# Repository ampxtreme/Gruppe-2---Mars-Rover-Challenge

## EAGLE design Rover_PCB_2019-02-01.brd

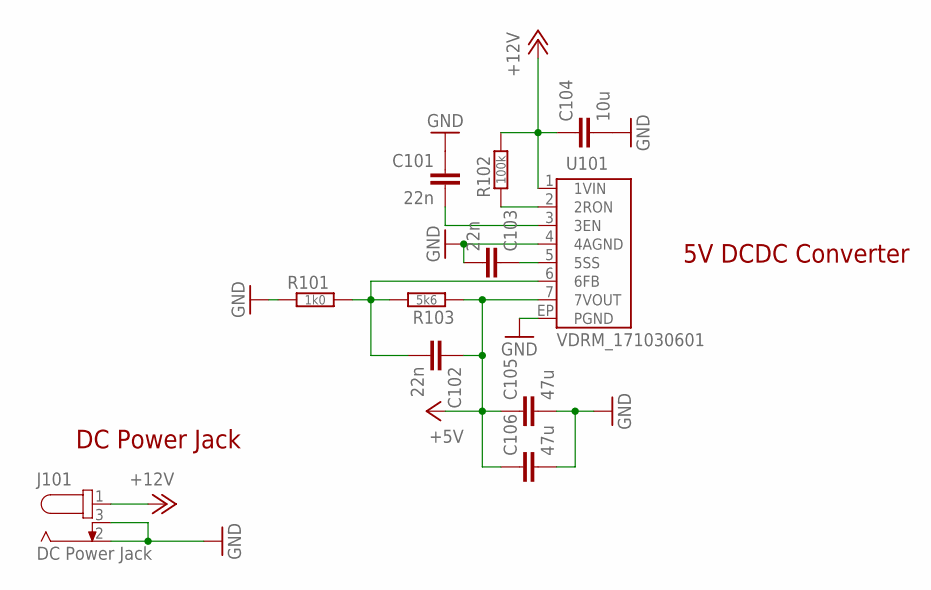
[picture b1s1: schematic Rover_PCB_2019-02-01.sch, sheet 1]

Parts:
C101, C102, C103: 22n; CAPC2012X95N
C104: 10u; CAP-US1210-EU3225
C105, C106: 47u; CAP-US1210-EU3225
J101: DC Power Jack; 69410X105102
R101: 1k0; RESC2012X50N
R102: 100k; RESC2012X50N
R103: 5k6; RESC2012X50N
U101: VDRM_171030601; VDRM_7PIN-PFM

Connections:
+5V: C102.1, C105.1, C106.1, R103.1, U101.7 (7VOUT); also elsewhere on the board
+12V: C104.1, J101.1, R102.2, U101.1 (1VIN); also elsewhere on the board
GND: C101.1, C103.2, C104.2, C105.2, C106.2, J101.2, J101.3, R101.1, U101.4 (4AGND), U101.EP (PGND); also elsewhere on the board
unnamed: R102.1, U101.2 (2RON)
unnamed: C103.1, U101.5 (5SS)
unnamed: C102.2, R101.2, R103.2, U101.6 (6FB)
unnamed: C101.2, U101.3 (3EN)

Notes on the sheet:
5V DCDC Converter
DC Power Jack

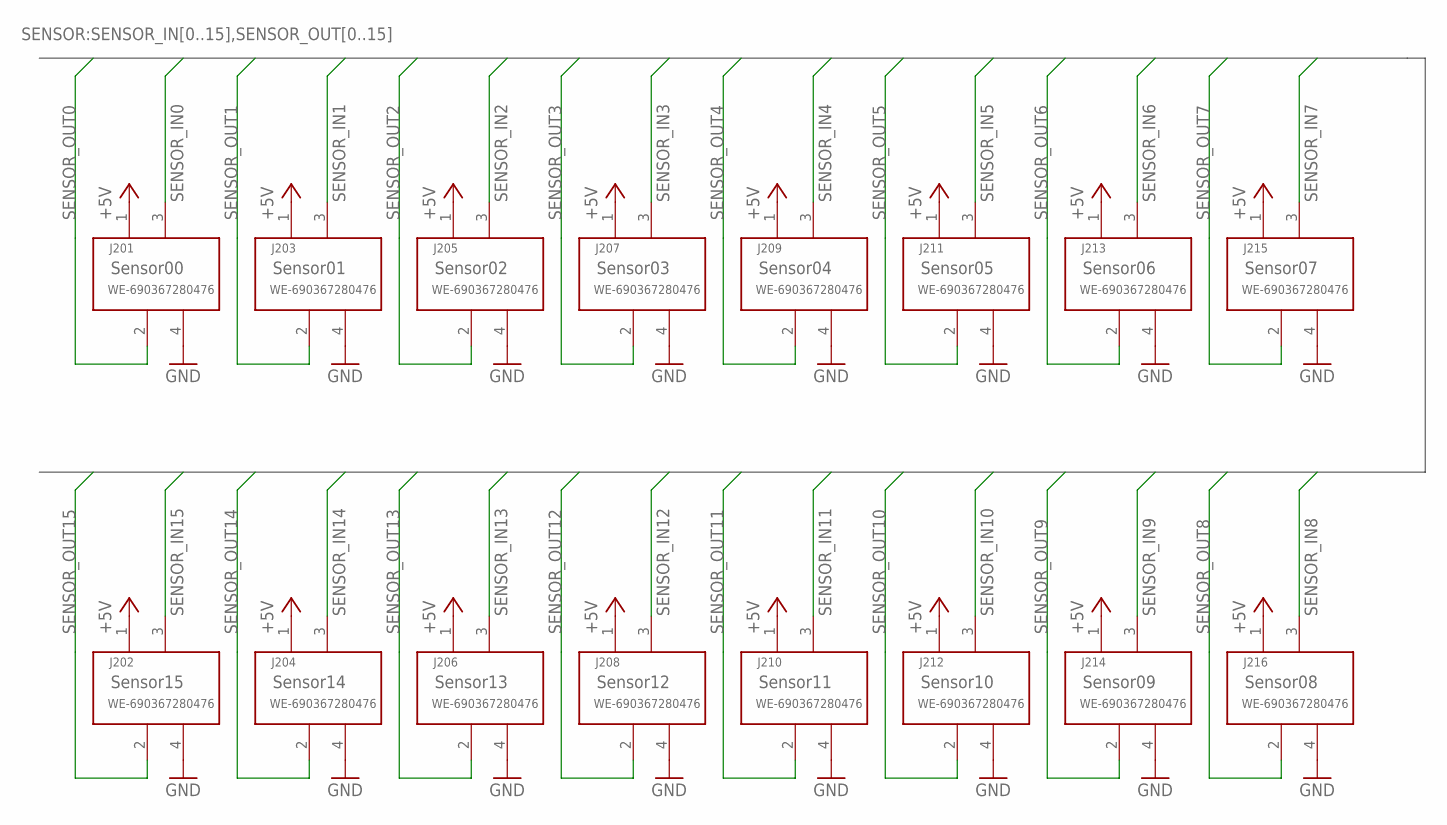
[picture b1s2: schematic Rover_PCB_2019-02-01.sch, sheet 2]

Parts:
J201, J202, J203, J204, J205, J206, J207, J208, J209, J210, J211, J212, J213, J214, J215, J216: WE-690367280476; 690367280476

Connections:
+5V: J201.1 (4), J202.1 (4), J203.1 (4), J204.1 (4), J205.1 (4), J206.1 (4), J207.1 (4), J208.1 (4), J209.1 (4), J210.1 (4), J211.1 (4), J212.1 (4), J213.1 (4), J214.1 (4), J215.1 (4), J216.1 (4); also elsewhere on the board
GND: J201.4 (1), J202.4 (1), J203.4 (1), J204.4 (1), J205.4 (1), J206.4 (1), J207.4 (1), J208.4 (1), J209.4 (1), J210.4 (1), J211.4 (1), J212.4 (1), J213.4 (1), J214.4 (1), J215.4 (1), J216.4 (1); also elsewhere on the board
SENSOR_IN0: J201.3 (2); also elsewhere on the board
SENSOR_IN1: J203.3 (2); also elsewhere on the board
SENSOR_IN2: J205.3 (2); also elsewhere on the board
SENSOR_IN3: J207.3 (2); also elsewhere on the board
SENSOR_IN4: J209.3 (2); also elsewhere on the board
SENSOR_IN5: J211.3 (2); also elsewhere on the board
SENSOR_IN6: J213.3 (2); also elsewhere on the board
SENSOR_IN7: J215.3 (2); also elsewhere on the board
SENSOR_IN8: J216.3 (2); also elsewhere on the board
SENSOR_IN9: J214.3 (2); also elsewhere on the board
SENSOR_IN10: J212.3 (2); also elsewhere on the board
SENSOR_IN11: J210.3 (2); also elsewhere on the board
SENSOR_IN12: J208.3 (2); also elsewhere on the board
SENSOR_IN13: J206.3 (2); also elsewhere on the board
SENSOR_IN14: J204.3 (2); also elsewhere on the board
SENSOR_IN15: J202.3 (2); also elsewhere on the board
SENSOR_OUT0: J201.2 (3); also elsewhere on the board
SENSOR_OUT1: J203.2 (3); also elsewhere on the board
SENSOR_OUT2: J205.2 (3); also elsewhere on the board
SENSOR_OUT3: J207.2 (3); also elsewhere on the board
SENSOR_OUT4: J209.2 (3); also elsewhere on the board
SENSOR_OUT5: J211.2 (3); also elsewhere on the board
SENSOR_OUT6: J213.2 (3); also elsewhere on the board
SENSOR_OUT7: J215.2 (3); also elsewhere on the board
SENSOR_OUT8: J216.2 (3); also elsewhere on the board
SENSOR_OUT9: J214.2 (3); also elsewhere on the board
SENSOR_OUT10: J212.2 (3); also elsewhere on the board
SENSOR_OUT11: J210.2 (3); also elsewhere on the board
SENSOR_OUT12: J208.2 (3); also elsewhere on the board
SENSOR_OUT13: J206.2 (3); also elsewhere on the board
SENSOR_OUT14: J204.2 (3); also elsewhere on the board
SENSOR_OUT15: J202.2 (3); also elsewhere on the board

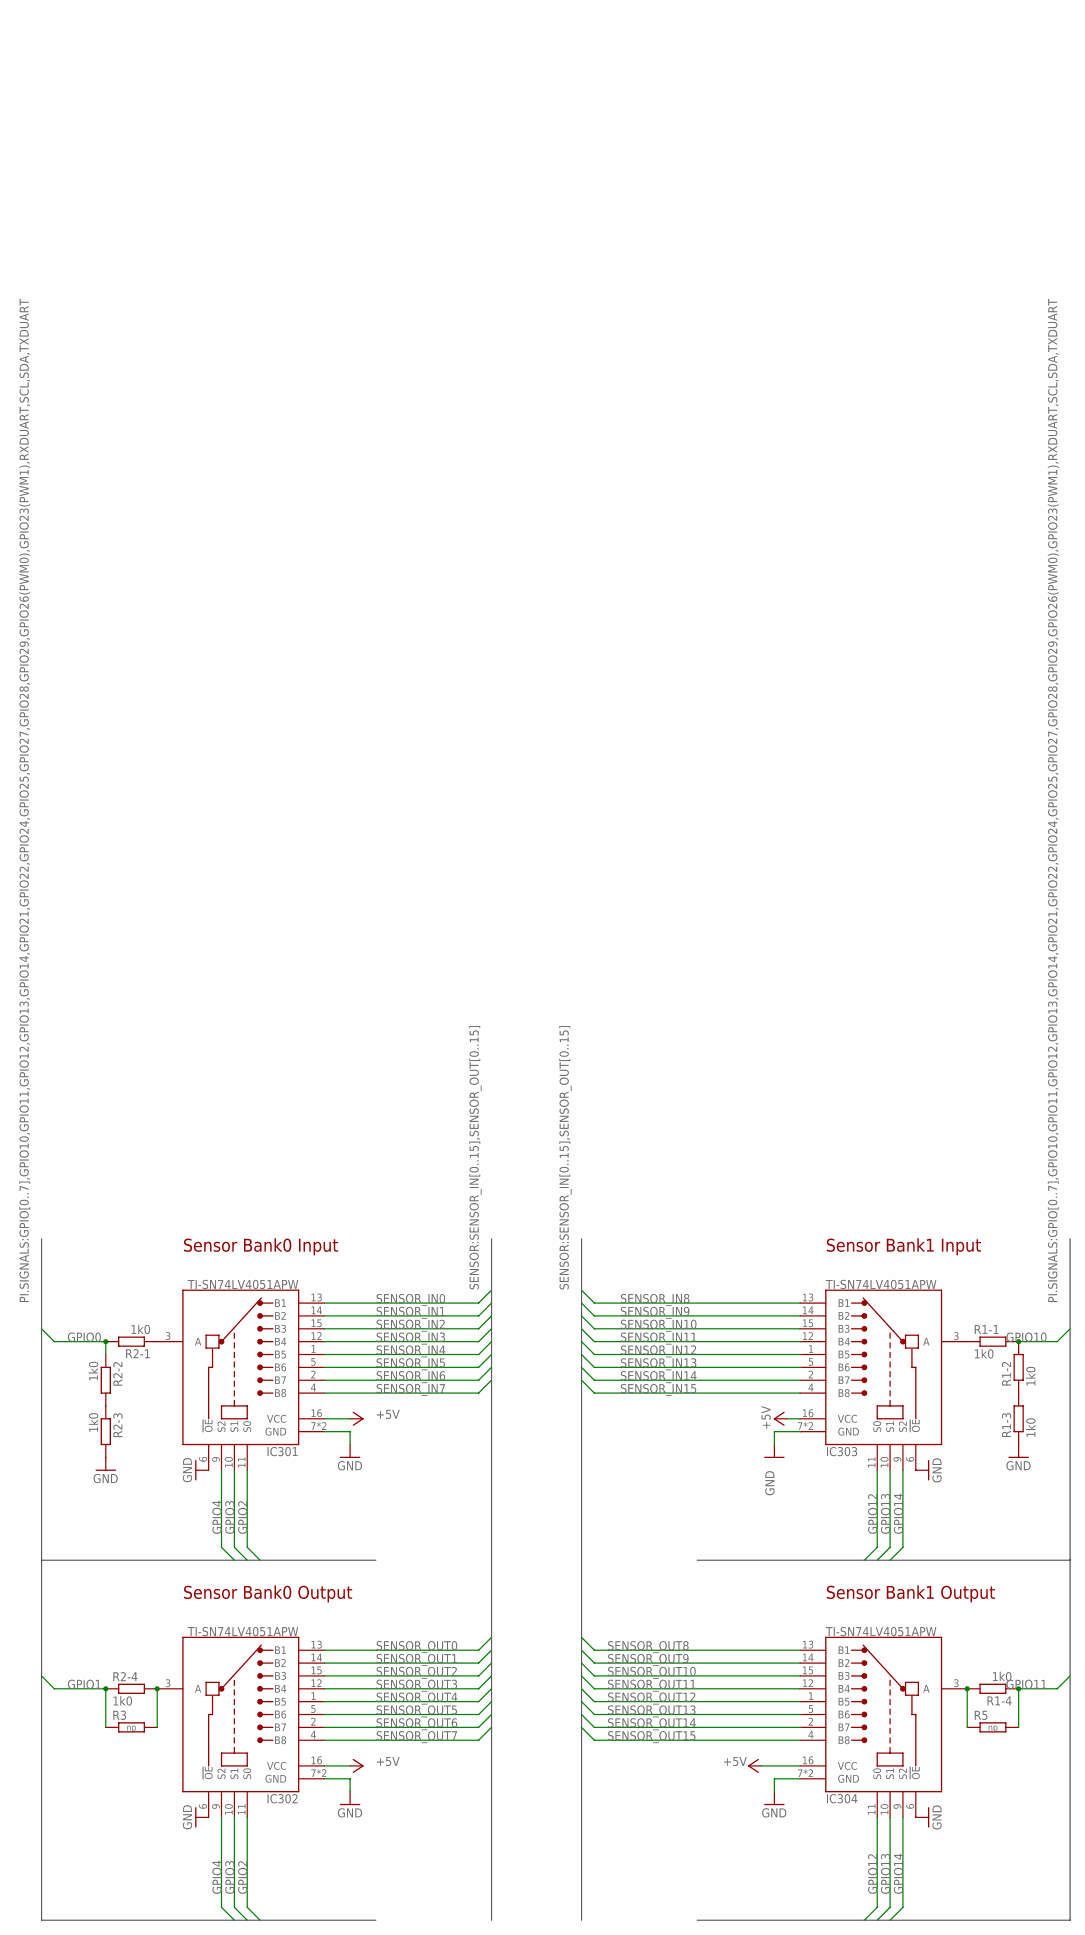
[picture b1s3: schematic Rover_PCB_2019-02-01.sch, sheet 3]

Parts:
IC301, IC302, IC303, IC304: TI-SN74LV4051APW; SOP16P65_500X640X120L62X24L
R1, R2: 1k0; CAPCAF80P160X320X70-8L
R3, R5: np; RESC2012X50N

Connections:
+5V: IC301.16 (VCC), IC302.16 (VCC), IC303.16 (VCC), IC304.16 (VCC); also elsewhere on the board
GND: IC301.6 (!OE), IC301.7 (GND), IC301.8 (GND), IC302.6 (!OE), IC302.7 (GND), IC302.8 (GND), IC303.6 (!OE), IC303.7 (GND), IC303.8 (GND), IC304.6 (!OE), IC304.7 (GND), IC304.8 (GND), R1.3 (1), R2.6 (2); also elsewhere on the board
GPIO0: R2.2 (1), R2.8 (2); also elsewhere on the board
GPIO1: R2.4 (1), R3.1; also elsewhere on the board
GPIO2: IC301.11 (S0), IC302.11 (S0); also elsewhere on the board
GPIO3: IC301.10 (S1), IC302.10 (S1); also elsewhere on the board
GPIO4: IC301.9 (S2), IC302.9 (S2); also elsewhere on the board
GPIO10: R1.7 (2), R1.8 (2); also elsewhere on the board
GPIO11: R1.4 (1), R5.2; also elsewhere on the board
GPIO12: IC303.11 (S0), IC304.11 (S0); also elsewhere on the board
GPIO13: IC303.10 (S1), IC304.10 (S1); also elsewhere on the board
GPIO14: IC303.9 (S2), IC304.9 (S2); also elsewhere on the board
unnamed: R1.2 (1), R1.6 (2)
unnamed: IC302.3 (A), R2.5 (2), R3.2
unnamed: IC304.3 (A), R1.5 (2), R5.1
unnamed: R2.3 (1), R2.7 (2)
unnamed: IC301.3 (A), R2.1
unnamed: IC303.3 (A), R1.1
SENSOR_IN0: IC301.13 (B1); also elsewhere on the board
SENSOR_IN1: IC301.14 (B2); also elsewhere on the board
SENSOR_IN2: IC301.15 (B3); also elsewhere on the board
SENSOR_IN3: IC301.12 (B4); also elsewhere on the board
SENSOR_IN4: IC301.1 (B5); also elsewhere on the board
SENSOR_IN5: IC301.5 (B6); also elsewhere on the board
SENSOR_IN6: IC301.2 (B7); also elsewhere on the board
SENSOR_IN7: IC301.4 (B8); also elsewhere on the board
SENSOR_IN8: IC303.13 (B1); also elsewhere on the board
SENSOR_IN9: IC303.14 (B2); also elsewhere on the board
SENSOR_IN10: IC303.15 (B3); also elsewhere on the board
SENSOR_IN11: IC303.12 (B4); also elsewhere on the board
SENSOR_IN12: IC303.1 (B5); also elsewhere on the board
SENSOR_IN13: IC303.5 (B6); also elsewhere on the board
SENSOR_IN14: IC303.2 (B7); also elsewhere on the board
SENSOR_IN15: IC303.4 (B8); also elsewhere on the board
SENSOR_OUT0: IC302.13 (B1); also elsewhere on the board
SENSOR_OUT1: IC302.14 (B2); also elsewhere on the board
SENSOR_OUT2: IC302.15 (B3); also elsewhere on the board
SENSOR_OUT3: IC302.12 (B4); also elsewhere on the board
SENSOR_OUT4: IC302.1 (B5); also elsewhere on the board
SENSOR_OUT5: IC302.5 (B6); also elsewhere on the board
SENSOR_OUT6: IC302.2 (B7); also elsewhere on the board
SENSOR_OUT7: IC302.4 (B8); also elsewhere on the board
SENSOR_OUT8: IC304.13 (B1); also elsewhere on the board
SENSOR_OUT9: IC304.14 (B2); also elsewhere on the board
SENSOR_OUT10: IC304.15 (B3); also elsewhere on the board
SENSOR_OUT11: IC304.12 (B4); also elsewhere on the board
SENSOR_OUT12: IC304.1 (B5); also elsewhere on the board
SENSOR_OUT13: IC304.5 (B6); also elsewhere on the board
SENSOR_OUT14: IC304.2 (B7); also elsewhere on the board
SENSOR_OUT15: IC304.4 (B8); also elsewhere on the board

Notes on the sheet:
Sensor Bank0 Input
Sensor Bank0 Output
Sensor Bank1 Input
Sensor Bank1 Output

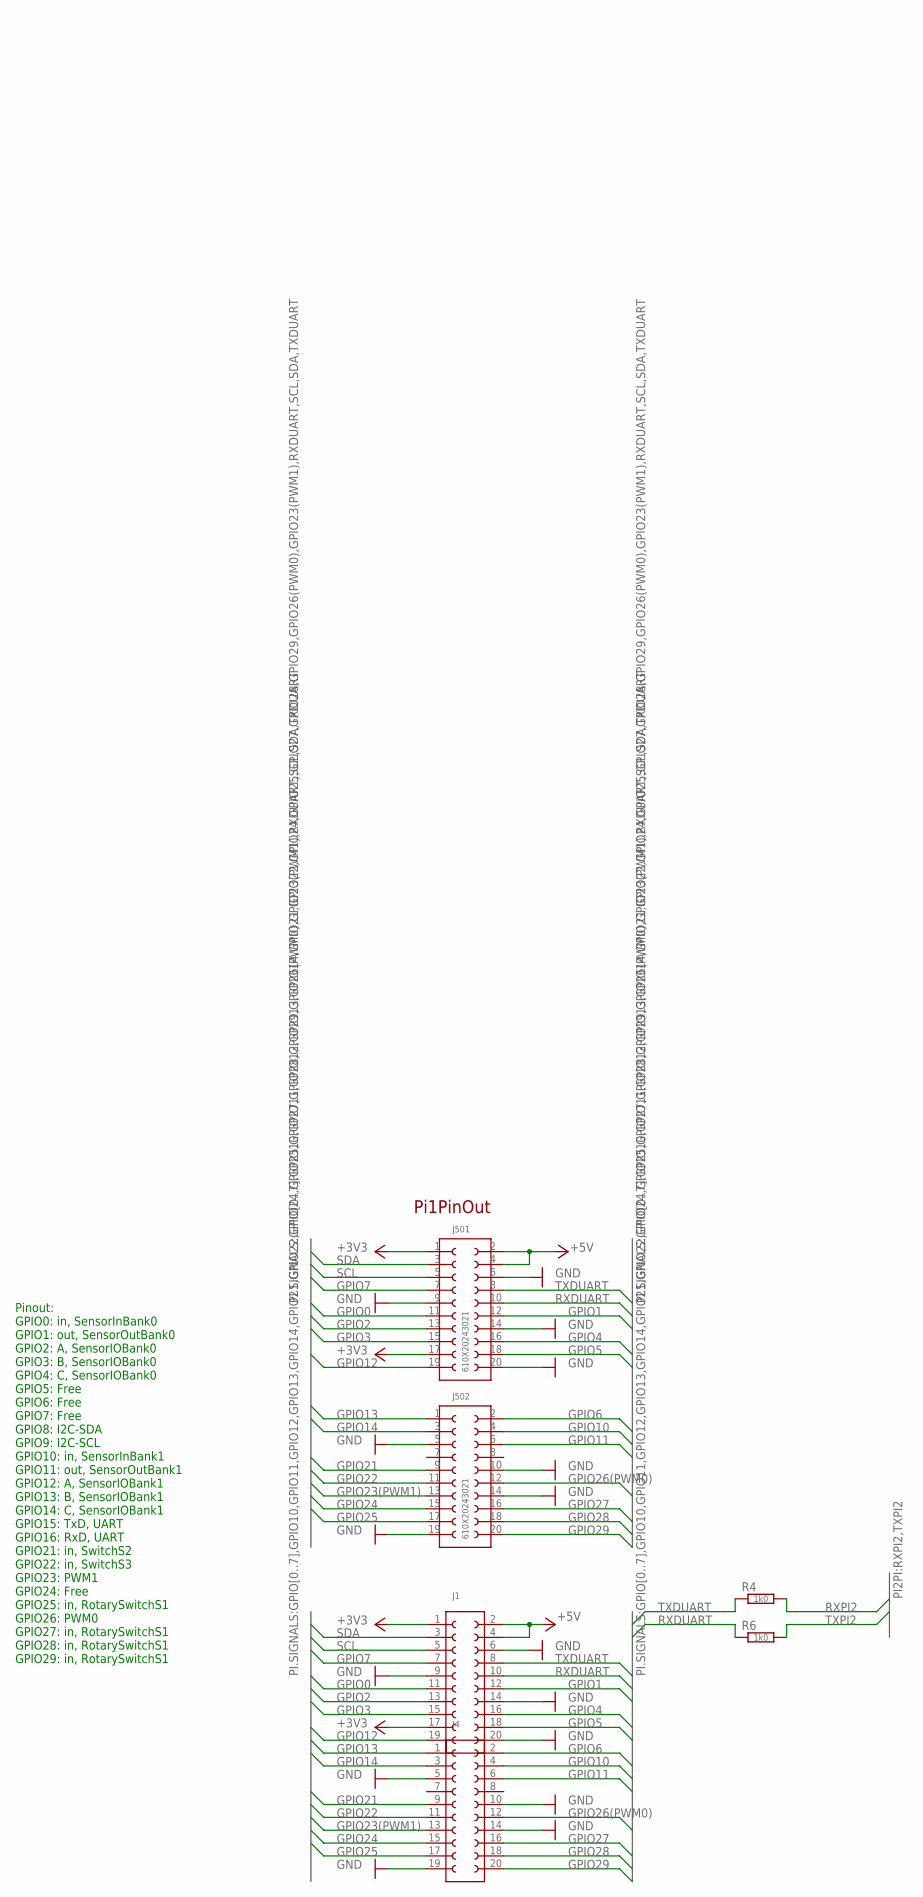
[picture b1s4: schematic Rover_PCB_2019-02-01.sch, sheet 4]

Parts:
J1, J4: 610X2021121
J501, J502: 610X20243021
R4, R6: 1k0; RESC2012X50N

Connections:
+3V3: J1.1, J1.17 (9), J501.1 (20), J501.17 (12); also elsewhere on the board
+5V: J1.2 (20), J1.4 (19), J501.2 (1), J501.4 (2); also elsewhere on the board
GND: J1.6 (18), J1.9 (5), J1.14, J1.20 (11), J4.5 (3), J4.10 (16), J4.14, J4.19 (10), J501.6 (3), J501.9 (16), J501.14 (7), J501.20 (10), J502.5 (18), J502.10 (5), J502.14 (7), J502.19 (11); also elsewhere on the board
GPIO0: J1.11 (6), J501.11 (15); also elsewhere on the board
GPIO1: J1.12 (15), J501.12 (6); also elsewhere on the board
GPIO2: J1.13 (7), J501.13 (14); also elsewhere on the board
GPIO3: J1.15 (8), J501.15 (13); also elsewhere on the board
GPIO4: J1.16 (13), J501.16 (8); also elsewhere on the board
GPIO5: J1.18 (12), J501.18 (9)
GPIO6: J4.2 (20), J502.2 (1)
GPIO7: J1.7 (4), J501.7 (17)
GPIO10: J4.4 (19), J502.4 (2); also elsewhere on the board
GPIO11: J4.6 (18), J502.6 (3); also elsewhere on the board
GPIO12: J1.19 (10), J501.19 (11); also elsewhere on the board
GPIO13: J4.1, J502.1 (20); also elsewhere on the board
GPIO14: J4.3 (2), J502.3 (19); also elsewhere on the board
GPIO21: J4.9 (5), J502.9 (16); also elsewhere on the board
GPIO22: J4.11 (6), J502.11 (15); also elsewhere on the board
GPIO23(PWM1): J4.13 (7), J502.13 (14); also elsewhere on the board
GPIO24: J4.15 (8), J502.15 (13)
GPIO25: J4.17 (9), J502.17 (12); also elsewhere on the board
GPIO26(PWM0): J4.12 (15), J502.12 (6); also elsewhere on the board
GPIO27: J4.16 (13), J502.16 (8); also elsewhere on the board
GPIO28: J4.18 (12), J502.18 (9); also elsewhere on the board
GPIO29: J4.20 (11), J502.20 (10); also elsewhere on the board
RXDUART: J1.10 (16), J501.10 (5), R6.1
RXPI2: R4.2; also elsewhere on the board
SCL: J1.5 (3), J501.5 (18); also elsewhere on the board
SDA: J1.3 (2), J501.3 (19); also elsewhere on the board
TXDUART: J1.8 (17), J501.8 (4), R4.1
TXPI2: R6.2; also elsewhere on the board

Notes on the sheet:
Pi1PinOut
Pinout: GPIO0: in, SensorInBank0 GPIO1: out, SensorOutBank0 GPIO2: A, SensorIOBank0 GPIO3: B, SensorIOBank0 GPIO4: C, SensorIOBank0 GPIO5: Free GPIO6: Free GPIO7: Free GPIO8: I2C-SDA GPIO9: I2C-SCL GPIO10: in, SensorInBank1 GPIO11: out, SensorOutBank1 GPIO12: A, SensorIOBank1 GPIO13: B, SensorIOBan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

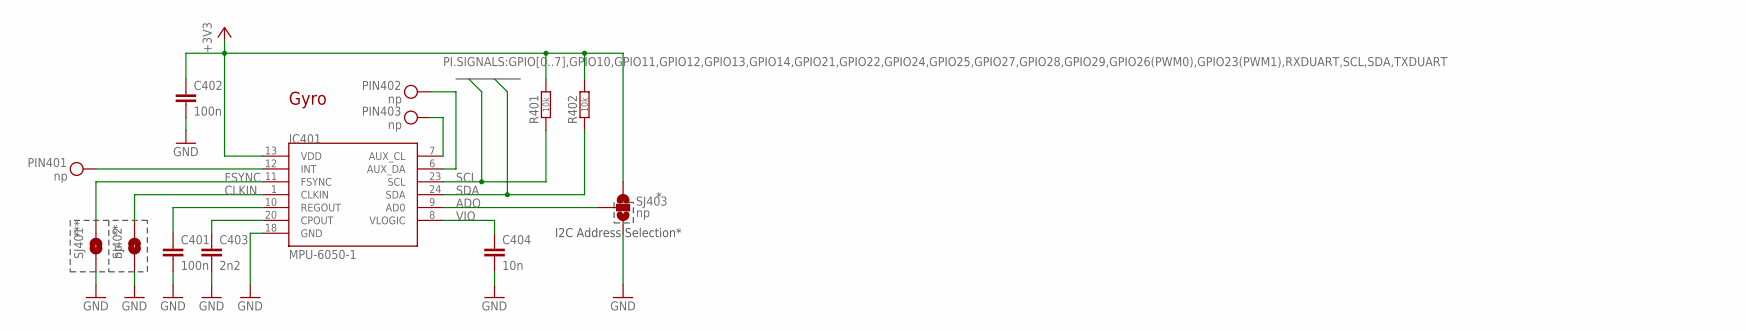
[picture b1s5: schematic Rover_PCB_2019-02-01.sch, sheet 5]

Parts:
C401, C402: 100n; CAPC2012X95N
C403: 2n2; CAPC2012X95N
C404: 10n; CAPC2012X95N
IC401: MPU-6050-1; QFN-24-4MM2
PIN401, PIN402, PIN403: np; SOLDER_PIN_0.5
R401, R402: 10k; RESC2012X50N
SJ401, SJ402: np; SJ_2S-TRACE
SJ403: np; SJ_3_PASTE1&2

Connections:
+3V3: C402.1, IC401.13 (VDD), R401.2, R402.2, SJ403.1; also elsewhere on the board
ADO: IC401.9 (AD0), SJ403.2
CLKIN: IC401.1 (CLKIN), SJ402.2
FSYNC: IC401.11 (FSYNC), SJ401.2
GND: C401.2, C402.2, C403.2, C404.2, IC401.18 (GND), SJ401.1, SJ402.1, SJ403.3; also elsewhere on the board
INT: IC401.12 (INT), PIN401._
unnamed: C403.1, IC401.20 (CPOUT)
unnamed: IC401.6 (AUX_DA), PIN402._
unnamed: C401.1, IC401.10 (REGOUT)
unnamed: IC401.7 (AUX_CL), PIN403._
SCL: IC401.23 (SCL), R401.1; also elsewhere on the board
SDA: IC401.24 (SDA), R402.1; also elsewhere on the board
VIO: C404.1, IC401.8 (VLOGIC)

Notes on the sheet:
I2C Address Selection*
***
Gyro

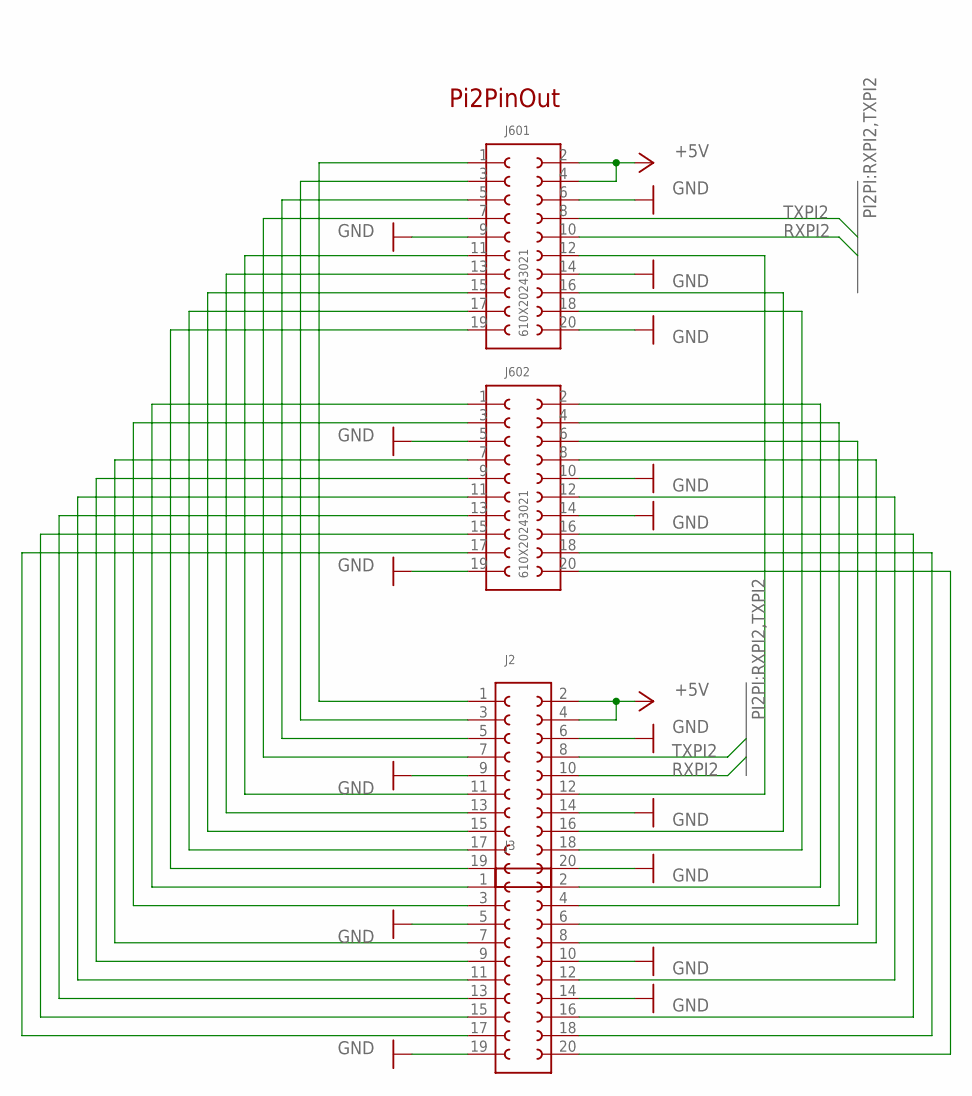
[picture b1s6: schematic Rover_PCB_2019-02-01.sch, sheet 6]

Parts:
J2, J3: 610X2021121
J601, J602: 610X20243021

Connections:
+5V: J2.2 (20), J2.4 (19), J601.2 (1), J601.4 (2); also elsewhere on the board
GND: J2.6 (18), J2.9 (5), J2.14, J2.20 (11), J3.5 (3), J3.10 (16), J3.14, J3.19 (10), J601.6 (3), J601.9 (16), J601.14 (7), J601.20 (10), J602.5 (18), J602.10 (5), J602.14 (7), J602.19 (11); also elsewhere on the board
unnamed: J3.11 (6), J602.11 (15)
unnamed: J3.13 (7), J602.13 (14)
unnamed: J3.15 (8), J602.15 (13)
unnamed: J3.17 (9), J602.17 (12)
unnamed: J2.16 (13), J601.16 (8)
unnamed: J2.12 (15), J601.12 (6)
unnamed: J2.18 (12), J601.18 (9)
unnamed: J3.2 (20), J602.2 (1)
unnamed: J3.4 (19), J602.4 (2)
unnamed: J3.6 (18), J602.6 (3)
unnamed: J3.8 (17), J602.8 (4)
unnamed: J3.12 (15), J602.12 (6)
unnamed: J2.3 (2), J601.3 (19)
unnamed: J2.5 (3), J601.5 (18)
unnamed: J2.7 (4), J601.7 (17)
unnamed: J2.11 (6), J601.11 (15)
unnamed: J2.13 (7), J601.13 (14)
unnamed: J2.15 (8), J601.15 (13)
unnamed: J2.1, J601.1 (20)
unnamed: J2.19 (10), J601.19 (11)
unnamed: J3.1, J602.1 (20)
unnamed: J3.3 (2), J602.3 (19)
unnamed: J3.7 (4), J602.7 (17)
unnamed: J3.9 (5), J602.9 (16)
unnamed: J3.16 (13), J602.16 (8)
unnamed: J3.18 (12), J602.18 (9)
unnamed: J3.20 (11), J602.20 (10)
unnamed: J2.17 (9), J601.17 (12)
RXPI2: J2.10 (16), J601.10 (5); also elsewhere on the board
TXPI2: J2.8 (17), J601.8 (4); also elsewhere on the board

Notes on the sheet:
Pi2PinOut

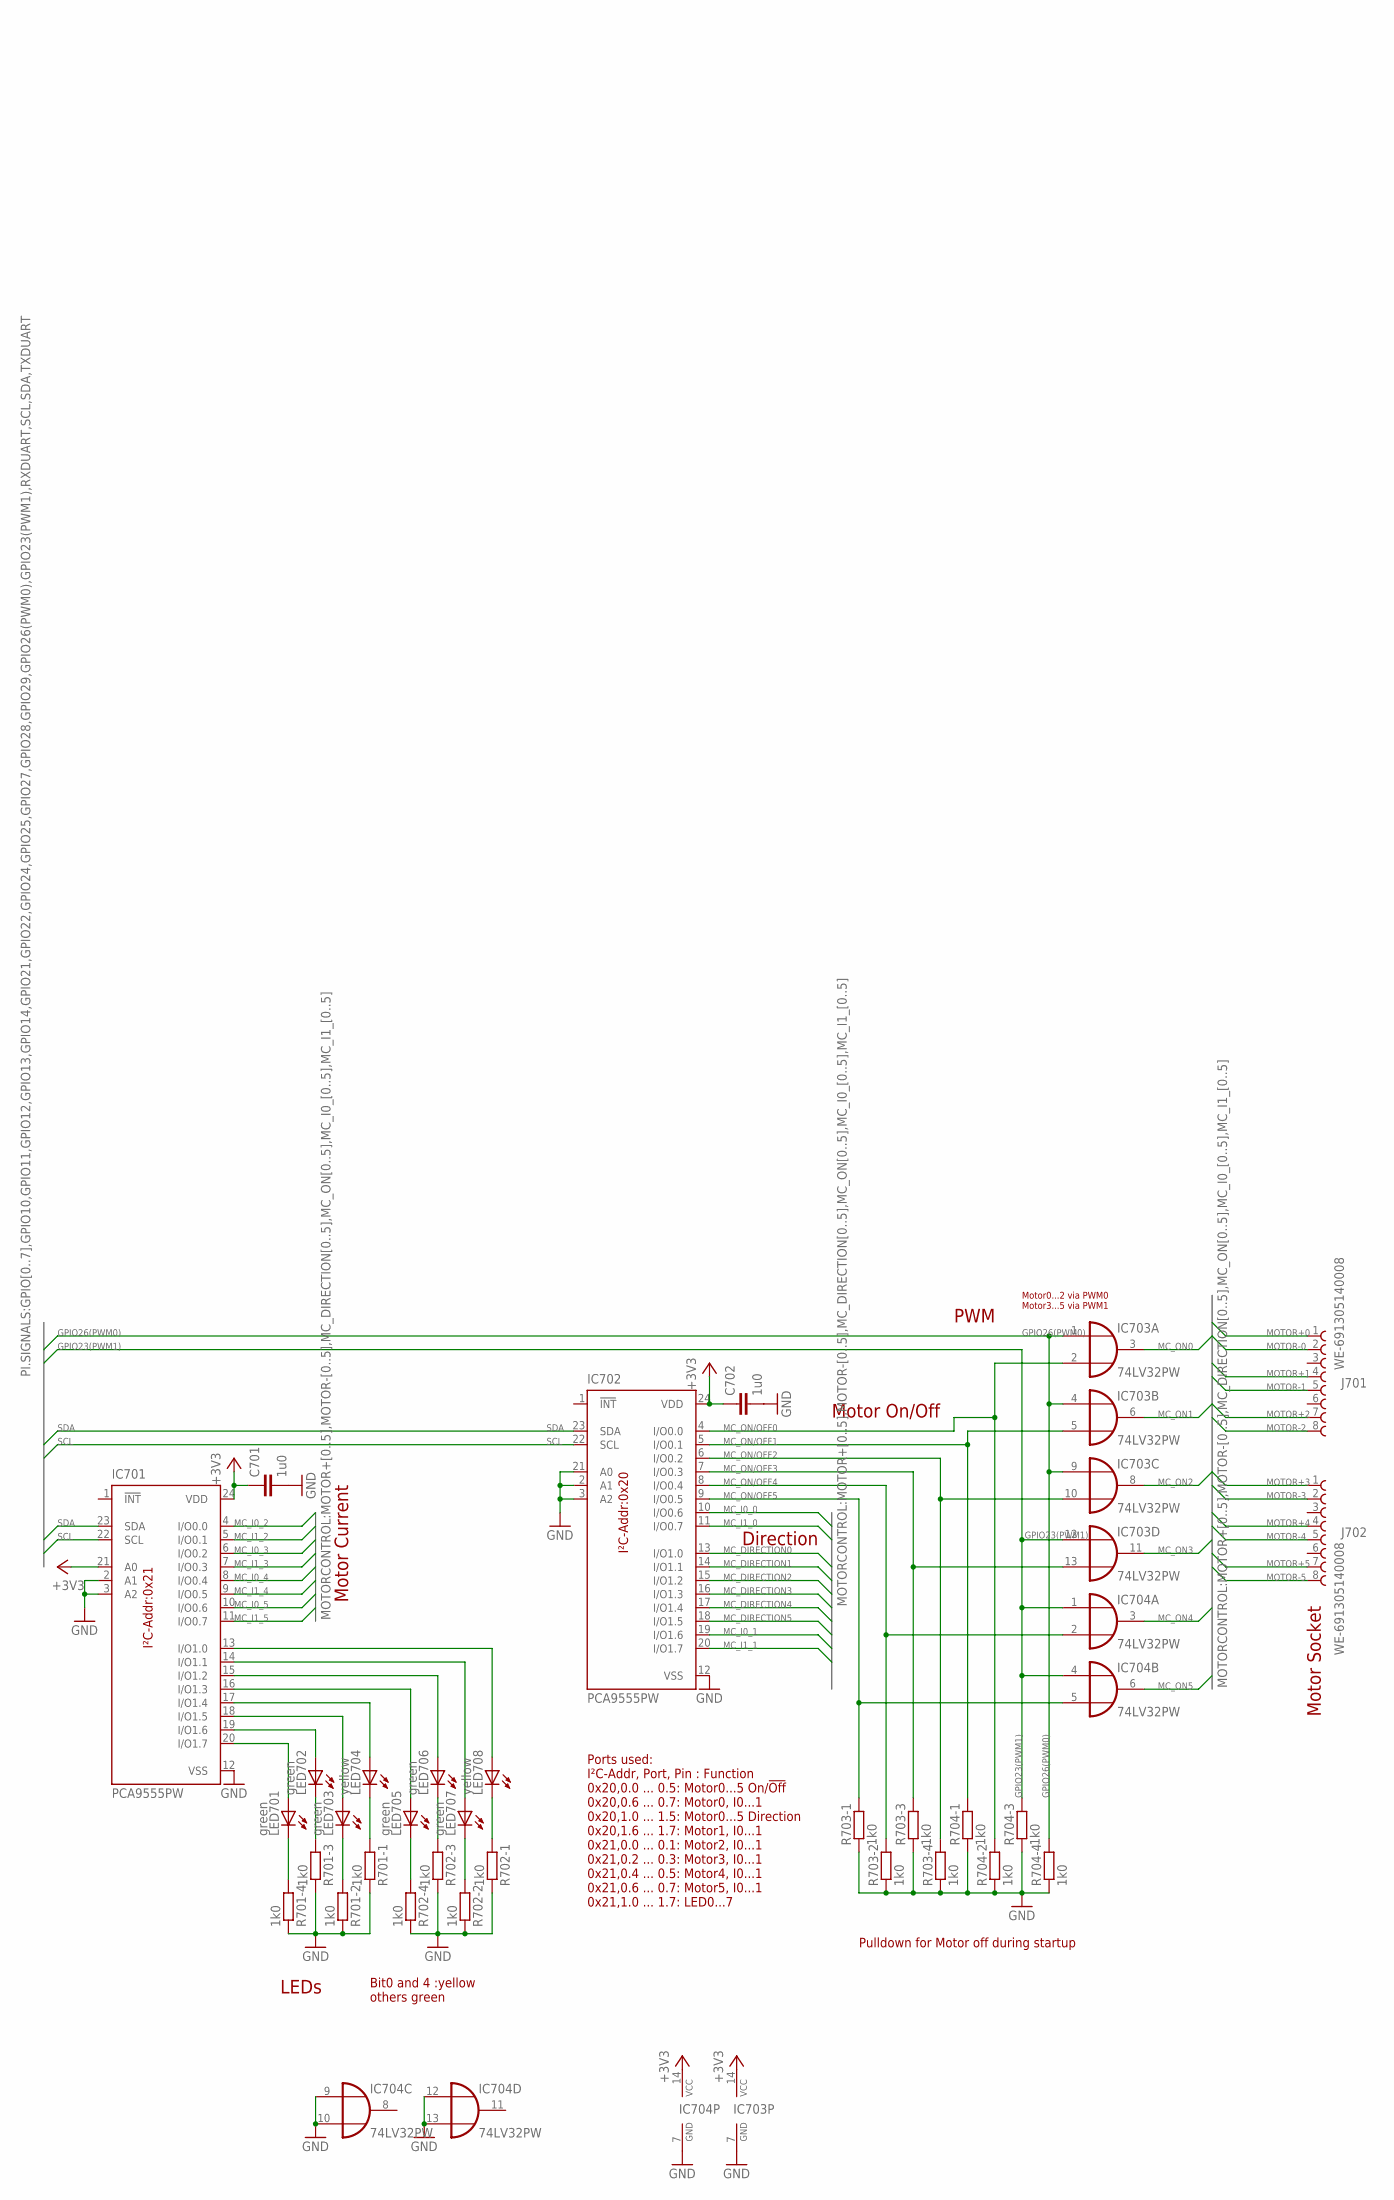
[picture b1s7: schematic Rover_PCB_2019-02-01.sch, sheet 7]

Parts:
C701, C702: 1u0; CAPC2012X95N
IC701, IC702: PCA9555PW; TSSOP24
IC703, IC704: 74LV32PW; SOP14P65_500X640X120L62X24L
J701, J702: WE-691305140008; 691305140008
LED701, LED702, LED703, LED705, LED706, LED707: green; LED-0603
LED704, LED708: yellow; LED-0603
R701, R702, R703, R704: 1k0; CAPCAF80P160X320X70-8L

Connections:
+3V3: C701.1, C702.1, IC701.21 (A0), IC701.24 (VDD), IC702.24 (VDD), IC703.14 (VCC), IC704.14 (VCC); also elsewhere on the board
GND: C701.2, C702.2, IC701.2 (A1), IC701.3 (A2), IC701.12 (VSS), IC702.2 (A1), IC702.3 (A2), IC702.12 (VSS), IC702.21 (A0), IC703.7 (GND), IC704.7 (GND), IC704.9 (I0), IC704.10 (I1), IC704.12 (I0), IC704.13 (I1), R701.1, R701.2 (1), R701.3 (1), R701.4 (1), R702.1, R702.2 (1), R702.3 (1), R702.4 (1), R703.1, R703.2 (1), R703.3 (1), R703.4 (1), R704.1, R704.2 (1), R704.3 (1), R704.4 (1); also elsewhere on the board
GPIO23(PWM1): IC703.12 (I0), IC704.1 (I0), IC704.4 (I0), R704.6 (2); also elsewhere on the board
GPIO26(PWM0): IC703.1 (I0), IC703.4 (I0), IC703.9 (I0), R704.5 (2); also elsewhere on the board
MC_DIRECTION0: IC702.13 (I/O1.0); also elsewhere on the board
MC_DIRECTION1: IC702.14 (I/O1.1); also elsewhere on the board
MC_DIRECTION2: IC702.15 (I/O1.2); also elsewhere on the board
MC_DIRECTION3: IC702.16 (I/O1.3); also elsewhere on the board
MC_DIRECTION4: IC702.17 (I/O1.4); also elsewhere on the board
MC_DIRECTION5: IC702.18 (I/O1.5); also elsewhere on the board
MC_I0_0: IC702.10 (I/O0.6); also elsewhere on the board
MC_I0_1: IC702.19 (I/O1.6); also elsewhere on the board
MC_I0_2: IC701.4 (I/O0.0); also elsewhere on the board
MC_I0_3: IC701.6 (I/O0.2); also elsewhere on the board
MC_I0_4: IC701.8 (I/O0.4); also elsewhere on the board
MC_I0_5: IC701.10 (I/O0.6); also elsewhere on the board
MC_I1_0: IC702.11 (I/O0.7); also elsewhere on the board
MC_I1_1: IC702.20 (I/O1.7); also elsewhere on the board
MC_I1_2: IC701.5 (I/O0.1); also elsewhere on the board
MC_I1_3: IC701.7 (I/O0.3); also elsewhere on the board
MC_I1_4: IC701.9 (I/O0.5); also elsewhere on the board
MC_I1_5: IC701.11 (I/O0.7); also elsewhere on the board
MC_ON0: IC703.3 (O); also elsewhere on the board
MC_ON1: IC703.6 (O); also elsewhere on the board
MC_ON2: IC703.8 (O); also elsewhere on the board
MC_ON3: IC703.11 (O); also elsewhere on the board
MC_ON4: IC704.3 (O); also elsewhere on the board
MC_ON5: IC704.6 (O); also elsewhere on the board
MC_ON/OFF0: IC702.4 (I/O0.0), IC703.2 (I1), R704.7 (2)
MC_ON/OFF1: IC702.5 (I/O0.1), IC703.5 (I1), R704.8 (2)
MC_ON/OFF2: IC702.6 (I/O0.2), IC703.10 (I1), R703.5 (2)
MC_ON/OFF3: IC702.7 (I/O0.3), IC703.13 (I1), R703.6 (2)
MC_ON/OFF4: IC702.8 (I/O0.4), IC704.2 (I1), R703.7 (2)
MC_ON/OFF5: IC702.9 (I/O0.5), IC704.5 (I1), R703.8 (2)
MOTOR+0: J701.1 (8); also elsewhere on the board
MOTOR+1: J701.4 (5); also elsewhere on the board
MOTOR+2: J701.7 (2); also elsewhere on the board
MOTOR+3: J702.1 (8); also elsewhere on the board
MOTOR+4: J702.4 (5); also elsewhere on the board
MOTOR+5: J702.7 (2); also elsewhere on the board
MOTOR-0: J701.2 (7); also elsewhere on the board
MOTOR-1: J701.5 (4); also elsewhere on the board
MOTOR-2: J701.8 (1); also elsewhere on the board
MOTOR-3: J702.2 (7); also elsewhere on the board
MOTOR-4: J702.5 (4); also elsewhere on the board
MOTOR-5: J702.8 (1); also elsewhere on the board
unnamed: LED708.C, R702.8 (2)
unnamed: LED707.C, R702.7 (2)
unnamed: LED706.C, R702.6 (2)
unnamed: LED705.C, R702.5 (2)
unnamed: LED704.C, R701.8 (2)
unnamed: LED703.C, R701.7 (2)
unnamed: LED702.C, R701.6 (2)
unnamed: LED701.C, R701.5 (2)
unnamed: IC701.13 (I/O1.0), LED708.A
unnamed: IC701.14 (I/O1.1), LED707.A
unnamed: IC701.15 (I/O1.2), LED706.A
unnamed: IC701.16 (I/O1.3), LED705.A
unnamed: IC701.17 (I/O1.4), LED704.A
unnamed: IC701.18 (I/O1.5), LED703.A
unnamed: IC701.19 (I/O1.6), LED702.A
unnamed: IC701.20 (I/O1.7), LED701.A
SCL: IC701.22 (SCL), IC702.22 (SCL); also elsewhere on the board
SDA: IC701.23 (SDA), IC702.23 (SDA); also elsewhere on the board

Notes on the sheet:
PWM
Motor On/Off
Direction
Motor Current
LEDs
I²C-Addr:0x20
I²C-Addr:0x21
Ports used: I²C-Addr, Port, Pin : Function 0x20,0.0 ... 0.5: Motor0...5 On/!Off! 0x20,0.6 ... 0.7: Motor0, I0...1 0x20,1.0 ... 1.5: Motor0...5 Direction 0x20,1.6 ... 1.7: Motor1, I0...1 0x21,0.0 ... 0.1: Motor2, I0...1 0x21,0.2 ... 0.3: Motor3, I0...1 0x21,0.4 ... 0.5: Motor4, I0...1 0x21,0.6 ... 0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
Pulldown for Motor off during startup
Bit0 and 4 :yellow others green
Motor0...2 via PWM0 Motor3...5 via PWM1
Motor Socket

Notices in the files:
parts and their libraries:
Rover_bib: Created A. Bachmaier, K&K Prime Engineering GmbH (c) 2011
